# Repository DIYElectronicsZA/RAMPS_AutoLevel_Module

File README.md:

# RAMPS_AutoLevel_Module
Small adaptor module to shift a 12V inductive probe sensor to 5V Arduino compatible levels

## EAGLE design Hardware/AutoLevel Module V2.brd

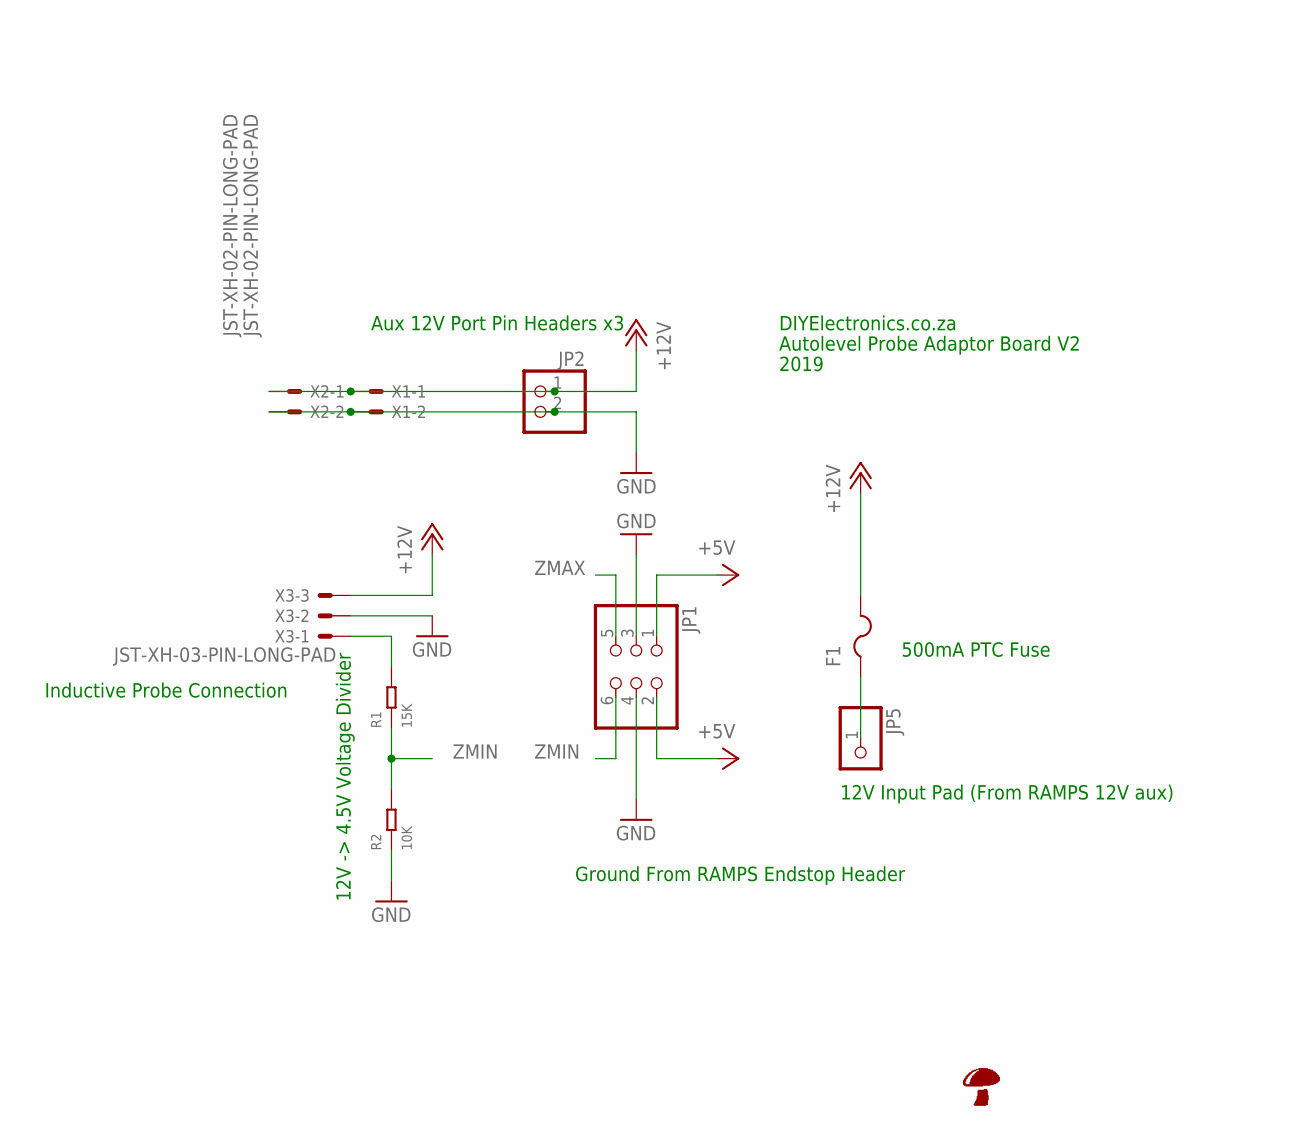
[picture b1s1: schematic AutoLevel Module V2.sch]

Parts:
F1: PTCFUSE-1812; 1812
JP1: PINHD-2X3; 2X03
JP2: PINHD-1X2; 1X02
JP5: PINHD-1X1; 1X01
R1: 15K; R0805
R2: 10K; R0805
U$2: SHROOMBOTTOMSILK; SHROOM_BS
X1, X2: JST-XH-02-PIN-LONG-PAD; JST-XH-02-PACKAGE-LONG-PAD
X3: JST-XH-03-PIN-LONG-PAD; JST-XH-03-PACKAGE-LONG-PAD

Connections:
+5V: JP1.1, JP1.2
+12V: F1.2, JP2.1, X1.1, X2.1, X3.3
GND: JP1.3, JP1.4, JP2.2, R2.1, X1.2, X2.2, X3.2
unnamed: F1.1, JP5.1
unnamed: R1.2, X3.1
ZMAX: JP1.5
ZMIN: JP1.6, R1.1, R2.2

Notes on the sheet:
Inductive Probe Connection
Aux 12V Port Pin Headers x3
12V Input Pad (From RAMPS 12V aux)
500mA PTC Fuse
12V -> 4.5V Voltage Divider
Ground From RAMPS Endstop Header
DIYElectronics.co.za
Autolevel Probe Adaptor Board V2
2019

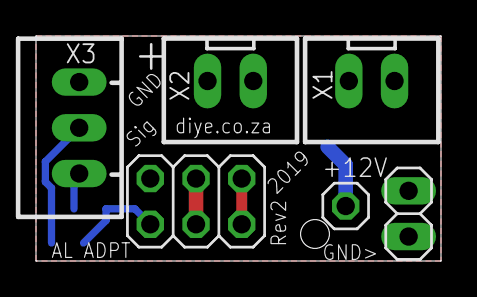
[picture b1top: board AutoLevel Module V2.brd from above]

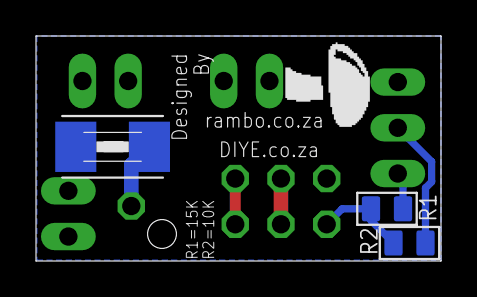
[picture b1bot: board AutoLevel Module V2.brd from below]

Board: 4 copper layers, 22.5 x 12.5 mm, 10 parts (4 on the bottom side), 6 nets.

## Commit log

2017-08-31 Inital transfer of v1.1 hardware
2019-10-07 Start Work on V2
2019-10-09 RFM V2
